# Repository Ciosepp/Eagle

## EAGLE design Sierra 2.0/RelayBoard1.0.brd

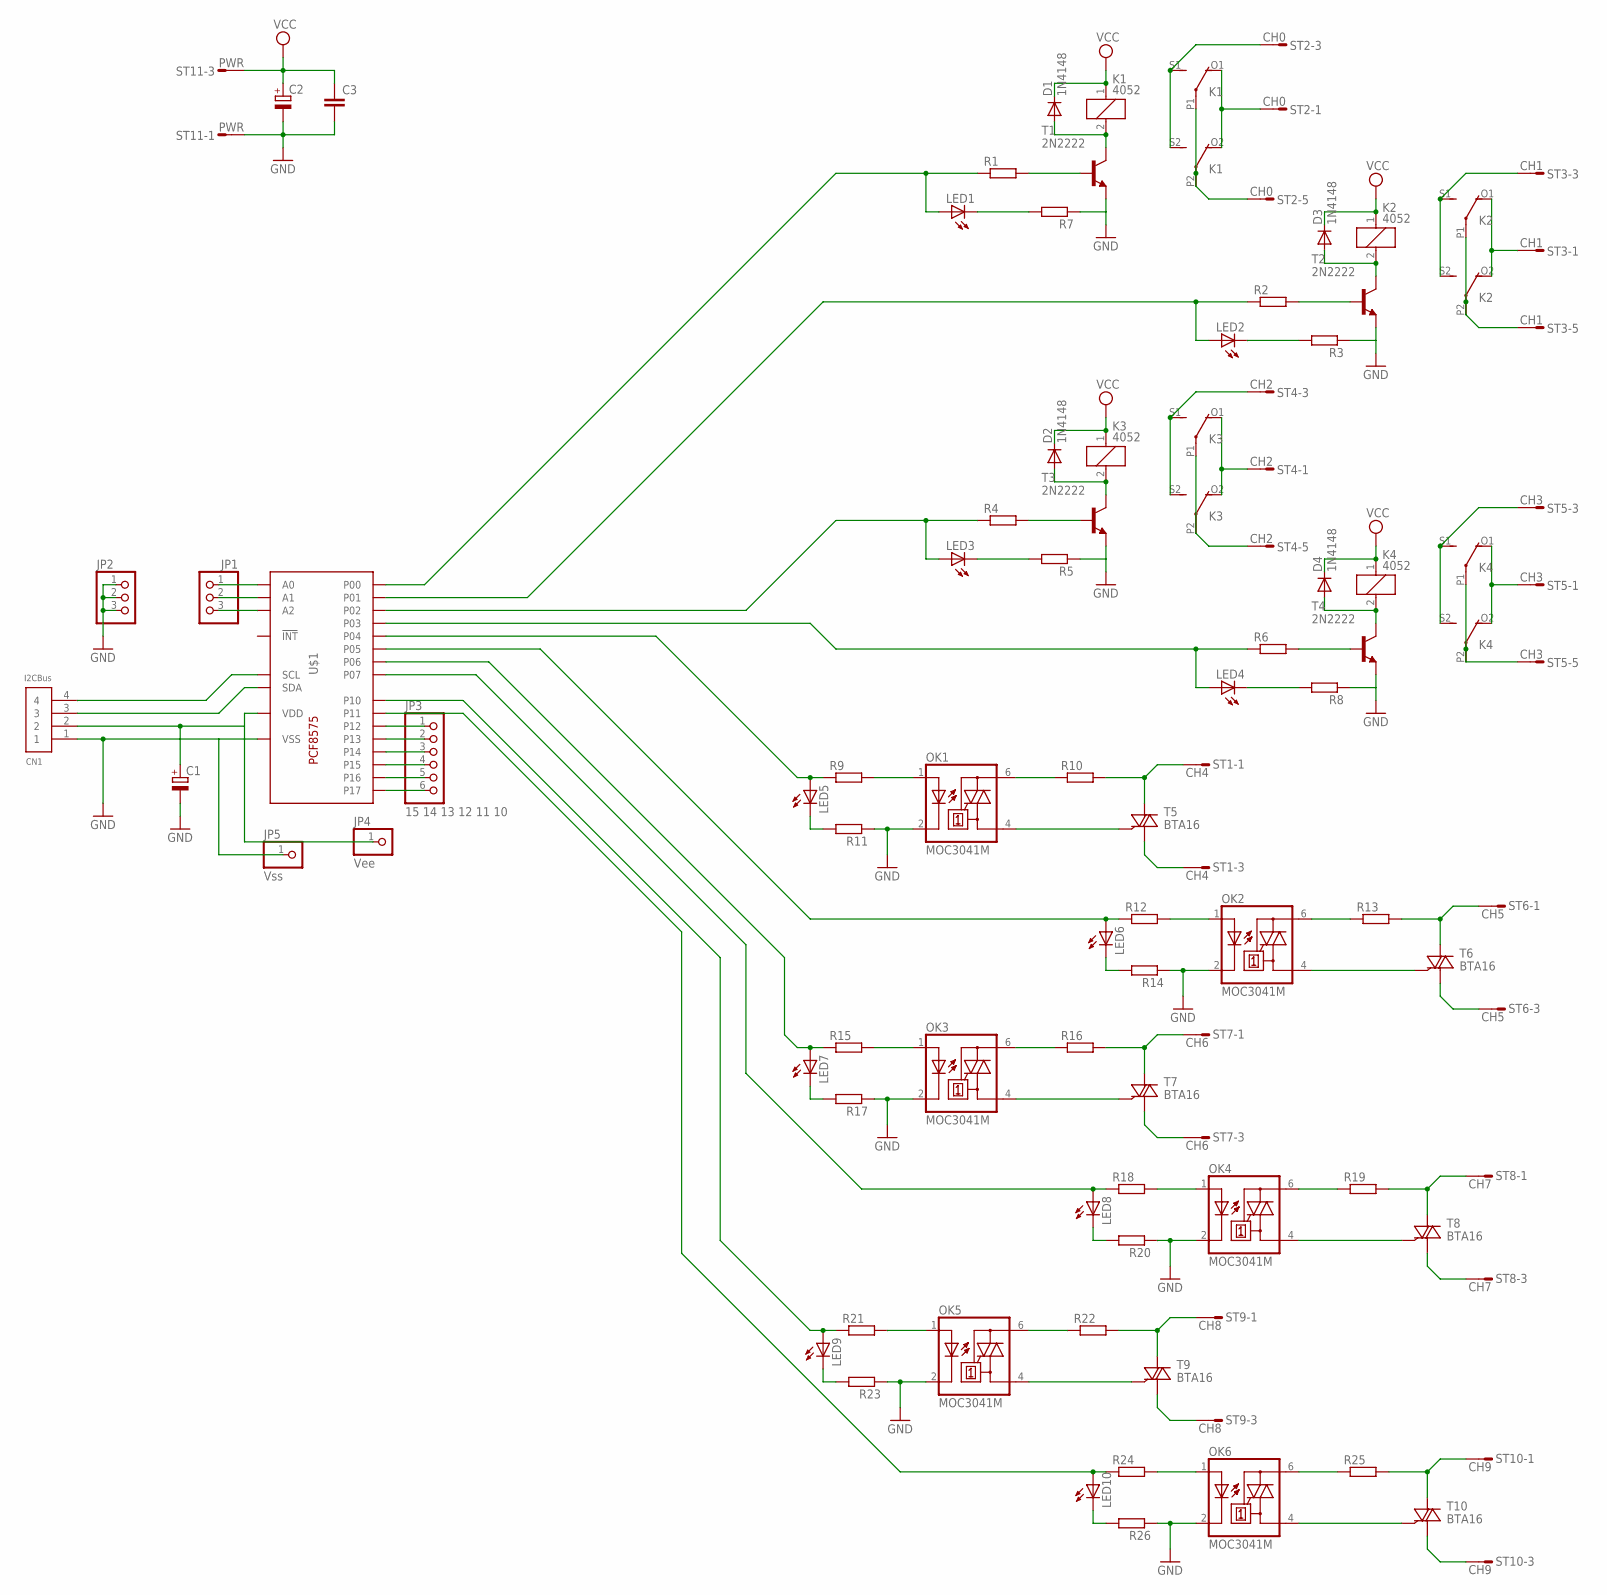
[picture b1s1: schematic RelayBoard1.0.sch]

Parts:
C1: CPOL-EUE3.5-8; E3,5-8
C2: CPOL-EUE2.5-7; E2,5-7
C3: C-EU050-025X075; C050-025X075
CN1: I2CBus; 1X04-BIG
D1, D2, D3, D4: 1N4148; DO35-7
JP1, JP2: PINHD-1X3; 1X03
JP3: 15 14 13 12 11 10; 1X06-CLEANBIG
JP4: Vee; 1X01-CLEANBIG
JP5: Vss; 1X01-CLEANBIG
K1, K2, K3, K4: 4052; F4052
LED1, LED2, LED3, LED4: LED3MM
LED5, LED6, LED7, LED8, LED9, LED10: LEDCHIPLED_0805; CHIPLED_0805
OK1, OK2, OK3, OK4, OK5, OK6: MOC3041M; DIL06
R1, R2, R4, R6: R-EU_0204/7; 0204/7
R3, R5, R7, R8, R9, R12, R15, R18, R21, R24: R-EU_0207/2V; 0207/2V
R10, R13, R16, R19, R22, R25: R-EU_0207/7; 0207/7
R11, R14, R17, R20, R23, R26: R-EU_M0805; M0805
ST1: CH4; MSF3
ST2: CH0; MSF5
ST3: CH1; MSF5
ST4: CH2; MSF5
ST5: CH3; MSF5
ST6: CH5; MSF3
ST7: CH6; MSF3
ST8: CH7; MSF3
ST9: CH8; MSF3
ST10: CH9; MSF3
ST11: PWR; MSF3
T1, T2, T3, T4: 2N2222; TO92-EBC-OVAL
T5, T6, T7, T8, T9, T10: BTA16; TO220BV
U$1: PCF8575C; SOP24

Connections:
GND: C1.-, C2.-, C3.2, CN1.1, JP2.1, JP2.2, JP2.3, JP5.1, OK1.2 (C), OK2.2 (C), OK3.2 (C), OK4.2 (C), OK5.2 (C), OK6.2 (C), R3.1, R5.1, R7.1, R8.1, R11.1, R14.1, R17.1, R20.1, R23.1, R26.1, ST11.1, T1.E, T2.E, T3.E, T4.E, U$1.P$12 (VSS)
unnamed: LED1.A, R1.1, U$1.P$4 (P00)
unnamed: C1.+, CN1.2, JP4.1, U$1.P$24 (VDD)
unnamed: LED1.K (C), R7.2
unnamed: LED2.A, R2.1, U$1.P$5 (P01)
unnamed: LED2.K (C), R3.2
unnamed: D3.A, K2.2, T2.C
unnamed: R2.2, T2.B
unnamed: LED3.A, R4.1, U$1.P$6 (P02)
unnamed: LED3.K (C), R5.2
unnamed: D1.A, K1.2, T1.C
unnamed: D2.A, K3.2, T3.C
unnamed: R4.2, T3.B
unnamed: R1.2, T1.B
unnamed: LED4.A, R6.1, U$1.P$7 (P03)
unnamed: LED4.K (C), R8.2
unnamed: D4.A, K4.2, T4.C
unnamed: R6.2, T4.B
unnamed: K2.O1 (O), K2.O2 (O), ST3.1
unnamed: CN1.3, U$1.P$23 (SDA)
unnamed: CN1.4, U$1.P$22 (SCL)
unnamed: JP1.1, U$1.P$21 (A0)
unnamed: JP1.2, U$1.P$2 (A1)
unnamed: JP1.3, U$1.P$3 (A2)
unnamed: LED5.A, R9.1, U$1.P$8 (P04)
unnamed: OK1.1 (A), R9.2
unnamed: ST1.3, T5.T1 (A1)
unnamed: OK1.4 (A1), T5.G
unnamed: OK1.6 (A2), R10.1
unnamed: R10.2, ST1.1, T5.T2 (A2)
unnamed: K1.S1 (S), K1.S2 (S), ST2.3
unnamed: K1.P1, K1.P2, ST2.5
unnamed: K1.O1 (O), K1.O2 (O), ST2.1
unnamed: K3.P1, K3.P2, ST4.5
unnamed: LED5.C, R11.2
unnamed: LED6.A, R12.1, U$1.P$9 (P05)
unnamed: K3.S1 (S), K3.S2 (S), ST4.3
unnamed: OK2.1 (A), R12.2
unnamed: K3.O1 (O), K3.O2 (O), ST4.1
unnamed: OK2.4 (A1), T6.G
unnamed: OK2.6 (A2), R13.1
unnamed: K4.O1 (O), K4.O2 (O), ST5.1
unnamed: K2.S1 (S), K2.S2 (S), ST3.3
unnamed: K2.P1, K2.P2, ST3.5
unnamed: R13.2, ST6.1, T6.T2 (A2)
unnamed: ST6.3, T6.T1 (A1)
unnamed: LED6.C, R14.2
unnamed: LED7.A, R15.1, U$1.P$10 (P06)
unnamed: K4.S1 (S), K4.S2 (S), ST5.3
unnamed: K4.P1, K4.P2, ST5.5
unnamed: OK3.1 (A), R15.2
unnamed: OK3.4 (A1), T7.G
unnamed: OK3.6 (A2), R16.1
unnamed: R16.2, ST7.1, T7.T2 (A2)
unnamed: ST7.3, T7.T1 (A1)
unnamed: LED7.C, R17.2
unnamed: LED8.A, R18.1, U$1.P$11 (P07)
unnamed: OK4.1 (A), R18.2
unnamed: OK4.4 (A1), T8.G
unnamed: OK4.6 (A2), R19.1
unnamed: R19.2, ST8.1, T8.T2 (A2)
unnamed: ST8.3, T8.T1 (A1)
unnamed: LED8.C, R20.2
unnamed: LED9.A, R21.1, U$1.P$13 (P10)
unnamed: OK5.1 (A), R21.2
unnamed: OK5.4 (A1), T9.G
unnamed: OK5.6 (A2), R22.1
unnamed: R22.2, ST9.1, T9.T2 (A2)
unnamed: ST9.3, T9.T1 (A1)
unnamed: LED9.C, R23.2
unnamed: LED10.A, R24.1, U$1.P$14 (P11)
unnamed: OK6.1 (A), R24.2
unnamed: OK6.4 (A1), T10.G
unnamed: OK6.6 (A2), R25.1
unnamed: R25.2, ST10.1, T10.T2 (A2)
unnamed: ST10.3, T10.T1 (A1)
unnamed: LED10.C, R26.2
unnamed: JP3.1, U$1.P$15 (P12)
unnamed: JP3.2, U$1.P$16 (P13)
unnamed: JP3.3, U$1.P$17 (P14)
unnamed: JP3.4, U$1.P$18 (P15)
unnamed: JP3.5, U$1.P$19 (P16)
unnamed: JP3.6, U$1.P$20 (P17)
VCC: C2.+, C3.1, D1.C, D2.C, D3.C, D4.C, K1.1, K2.1, K3.1, K4.1, ST11.3

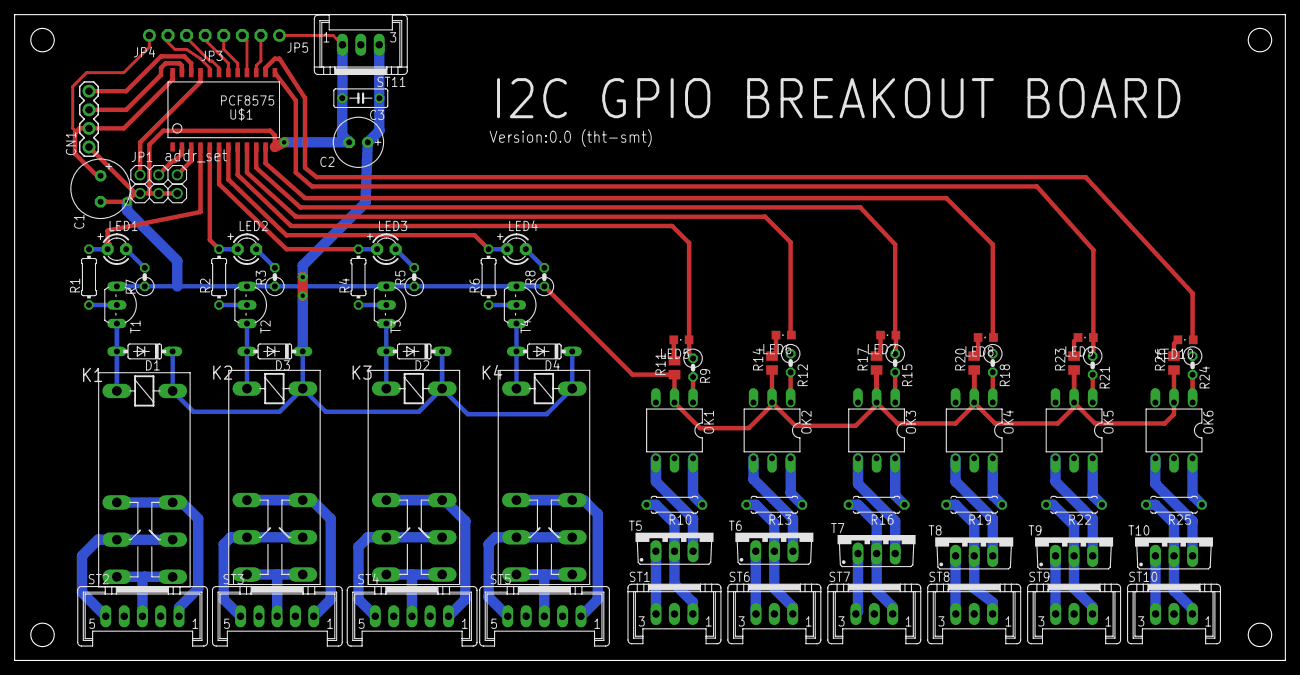
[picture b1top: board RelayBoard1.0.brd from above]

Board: 2 copper layers, 173.7 x 88.3 mm, 81 parts (0 on the bottom side), 84 nets.

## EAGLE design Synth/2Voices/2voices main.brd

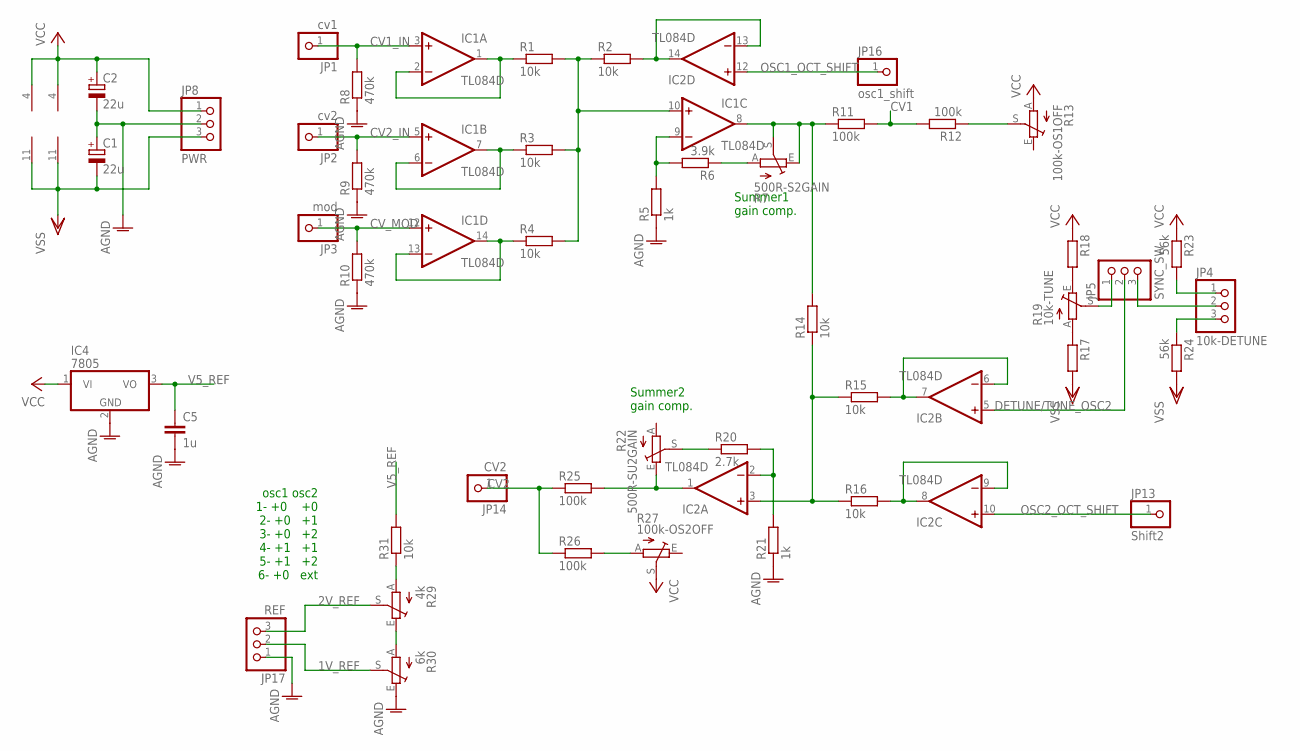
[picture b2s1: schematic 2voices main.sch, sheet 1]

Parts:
C1, C2: 22u; E2,5-7
C5: 1u; C0805
IC1, IC2: TL084D; SO14
IC4: 7805; TO220V
JP1: cv1; 1X01
JP2: cv2; 1X01
JP3: mod; 1X01
JP4: 10k-DETUNE; 1X03
JP5: SYNC_SW; 1X03
JP8: PWR; 1X03
JP13: Shift2; 1X01
JP14: CV2; 1X01
JP16: osc1_shift; 1X01
JP17: REF; 1X03
R1, R2, R3, R4, R14, R15, R16, R31: 10k; R0805
R5, R21: 1k; R0805
R6: 3.9k; R0805
R7: 500R-S2GAIN; S63S
R8, R9, R10: 470k; R0805
R11, R12, R25, R26: 100k; R0805
R13: 100k-OS1OFF; S63S
R17, R18: R-EU_R0805; R0805
R19: 10k-TUNE; S63S
R20: 2.7k; R0805
R22: 500R-SU2GAIN; S63S
R23, R24: 56k; R0805
R27: 100k-OS2OFF; S63S
R29: 4k; S63S
R30: 6k; S63S

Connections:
1V_REF: JP17.2, R30.S
2V_REF: JP17.3, R29.S
AGND: C1.+, C2.-, C5.2, IC4.2 (GND), JP8.2, JP17.1, R5.1, R8.1, R9.1, R10.1, R21.1, R30.E; also elsewhere on the board
CV1: R11.2, R12.2
CV1_IN: IC1.3 (+IN), JP1.1, R8.2
CV2: JP14.1, R25.1, R26.1
CV2_IN: IC1.5 (+IN), JP2.1, R9.2
CV_MOD: IC1.12 (+IN), JP3.1, R10.2
DETUNE/TUNE_OSC2: IC2.5 (+IN), JP5.2
unnamed: IC2.13 (-IN), IC2.14 (OUT), R2.2
unnamed: R29.E, R30.A
unnamed: IC1.1 (OUT), IC1.2 (-IN), R1.1
unnamed: R17.1, R19.A
unnamed: IC1.6 (-IN), IC1.7 (OUT), R3.1
unnamed: IC1.13 (-IN), IC1.14 (OUT), R4.1
unnamed: IC1.10 (+IN), R1.2, R2.1, R3.2, R4.2
unnamed: IC1.9 (-IN), R5.2, R6.2
unnamed: R6.1, R7.A
unnamed: R29.A, R31.1
unnamed: R12.1, R13.S
unnamed: IC1.8 (OUT), R7.E, R7.S, R11.1, R14.2
unnamed: R18.2, R19.E
unnamed: IC2.1 (OUT), R22.E, R25.2
unnamed: R20.1, R22.S
unnamed: IC2.2 (-IN), R20.2, R21.2
unnamed: IC2.3 (+IN), R14.1, R15.1, R16.1
unnamed: IC2.6 (-IN), IC2.7 (OUT), R15.2
unnamed: JP4.1, R23.2
unnamed: JP4.3, R24.1
unnamed: JP4.2, JP5.3
unnamed: JP5.1, R19.S
unnamed: IC2.8 (OUT), IC2.9 (-IN), R16.2
unnamed: R26.2, R27.A
OSC1_OCT_SHIFT: IC2.12 (+IN), JP16.1
OSC2_OCT_SHIFT: IC2.10 (+IN), JP13.1
V5_REF: C5.1, IC4.3 (VO), R31.2
VCC: C2.+, IC1.4 (V+), IC2.4 (V+), IC4.1 (VI), JP8.1, R13.A, R18.1, R23.1, R27.S; also elsewhere on the board
VSS: C1.-, IC1.11 (V-), IC2.11 (V-), JP8.3, R17.2, R24.2; also elsewhere on the board

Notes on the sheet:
osc1 osc2 1- +0 +0 2- +0 +1 3- +0 +2 4- +1 +1 5- +1 +2 6- +0 ext
Summer1 gain comp.
Summer2 gain comp.

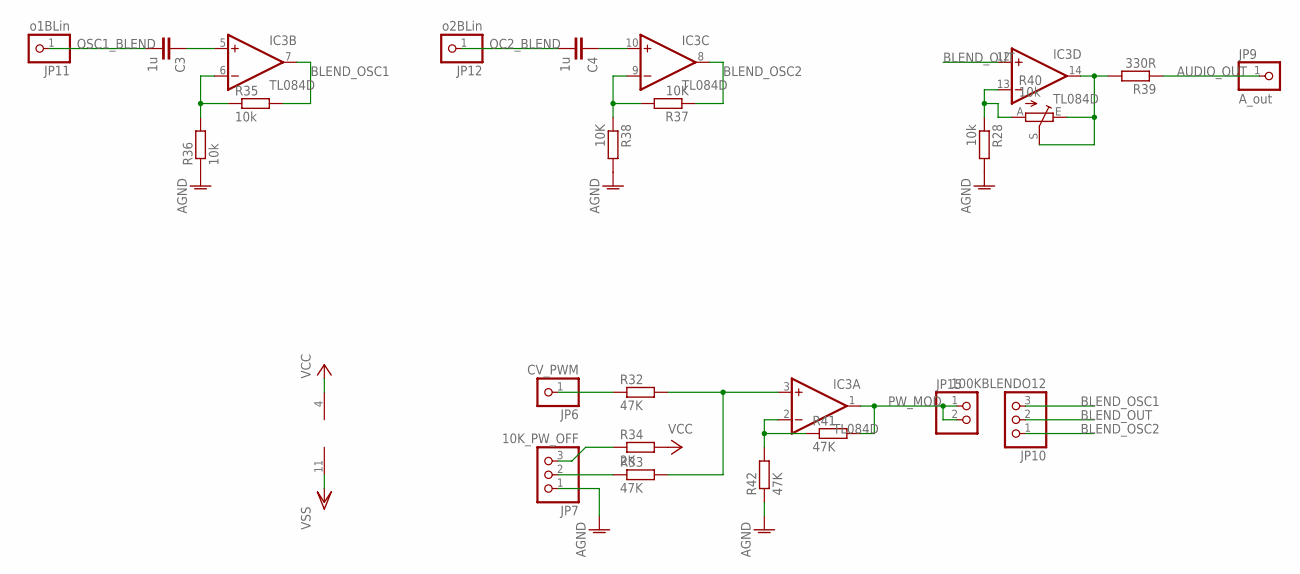
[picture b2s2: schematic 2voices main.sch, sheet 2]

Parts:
C3, C4: 1u; C0805
IC3: TL084D; SO14
JP6: CV_PWM; 1X01
JP7: 10K_PW_OFF; 1X03
JP9: A_out; 1X01
JP10: 100KBLENDO12; 1X03
JP11: o1BLin; 1X01
JP12: o2BLin; 1X01
JP15: PINHD-1X2; 1X02
R28, R35, R36: 10k; R0805
R32, R33, R41, R42: 47K; R0805
R34: 2K; R0805
R37, R38: 10K; R0805
R39: 330R; R0805
R40: 10k; S63S

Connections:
AGND: JP7.1, R28.2, R36.1, R38.2, R42.1; also elsewhere on the board
AUDIO_OUT: JP9.1, R39.1
BLEND_OSC1: IC3.7 (OUT), JP10.3, R35.2
BLEND_OSC2: IC3.8 (OUT), JP10.1, R37.1
BLEND_OUT: IC3.12 (+IN), JP10.2
unnamed: C3.1, IC3.5 (+IN)
unnamed: JP6.1, R32.1
unnamed: JP7.2, R33.1
unnamed: JP7.3, R34.1
unnamed: IC3.13 (-IN), R28.1, R40.A
unnamed: IC3.3 (+IN), R32.2, R33.2
unnamed: IC3.6 (-IN), R35.1, R36.2
unnamed: IC3.9 (-IN), R37.2, R38.1
unnamed: IC3.14 (OUT), R39.2, R40.E, R40.S
unnamed: C4.1, IC3.10 (+IN)
unnamed: IC3.2 (-IN), R41.1, R42.2
OC2_BLEND: C4.2, JP12.1
OSC1_BLEND: C3.2, JP11.1
PW_MOD: IC3.1 (OUT), JP15.1, JP15.2, R41.2
VCC: IC3.4 (V+), R34.2; also elsewhere on the board
VSS: IC3.11 (V-); also elsewhere on the board

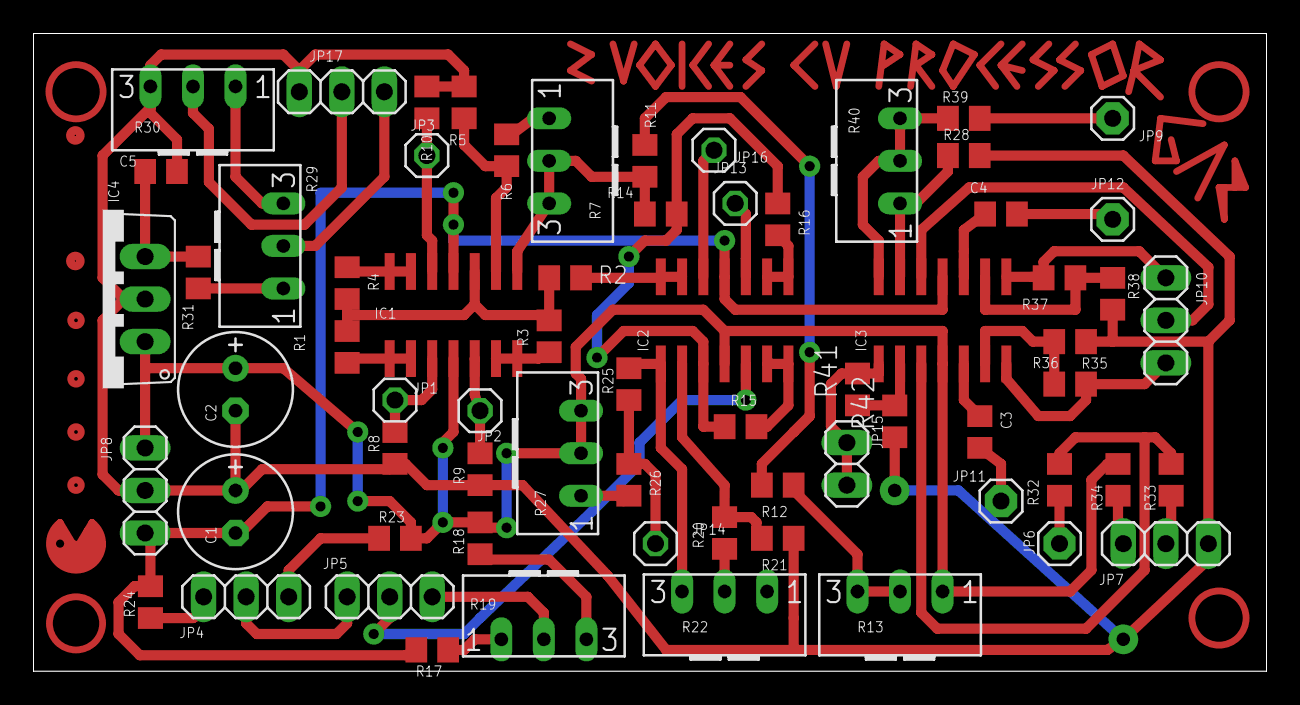
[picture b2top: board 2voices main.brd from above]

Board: 2 copper layers, 73.6 x 38.1 mm, 68 parts (0 on the bottom side), 56 nets.

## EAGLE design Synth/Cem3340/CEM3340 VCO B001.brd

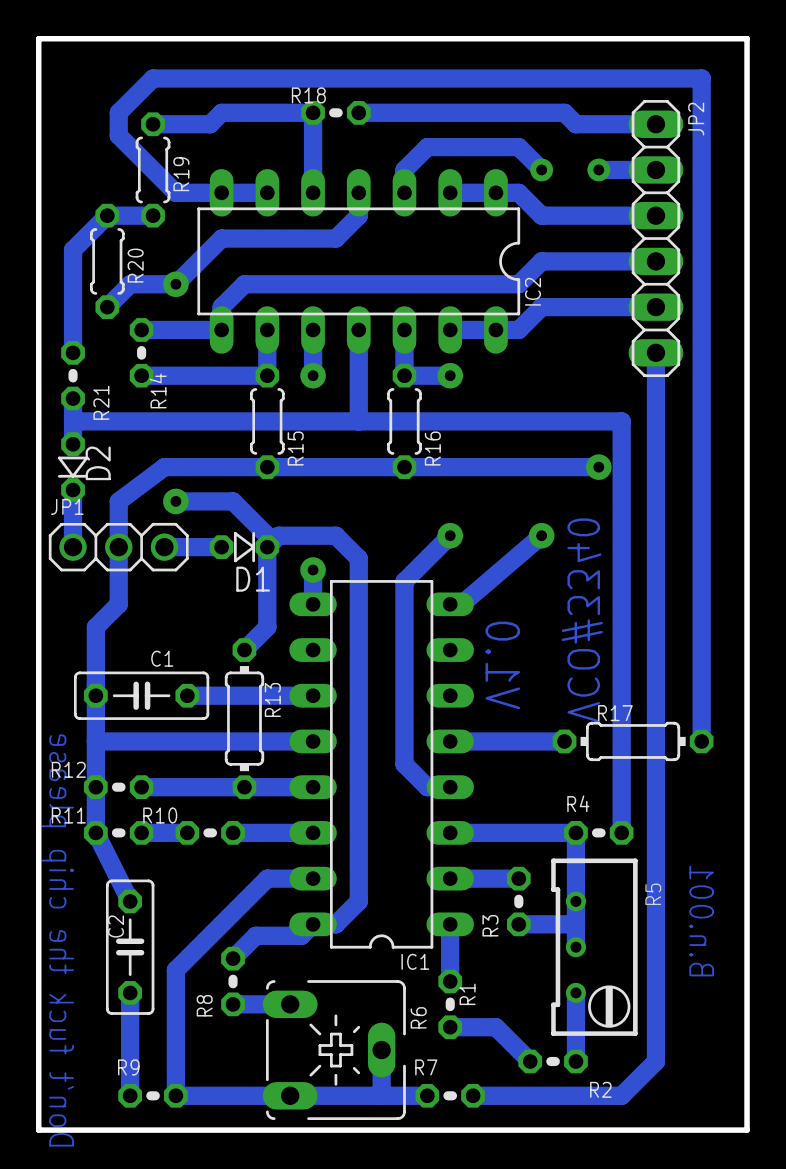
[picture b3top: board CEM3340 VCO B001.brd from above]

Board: 2 copper layers, 39.4 x 60.6 mm, 29 parts (0 on the bottom side), 30 nets.

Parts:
C1, C2: C050-025X075
D1, D2: D-2.5
IC1: CEM3340; DIL16
IC2: TL084P; DIL14
JP1: 1X03
JP2: 1X06
R1, R2, R3, R4, R7, R8, R9, R10, R11, R12, R14, R18, R21: 0204V
R5: RTRIM64W
R6: CA6V
R13, R17: 0204/7
R15, R16, R19, R20: 0204/5

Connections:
GND: C1.1, C2.2, IC1.12, JP1.2, JP2.2, R11.1, R12.2, R15.2, R16.2
unnamed: IC1.1, R1.2
unnamed: R1.1, R2.2
unnamed: R2.1, R5.3
unnamed: IC1.3, R3.1, R4.2, R5.1, R5.2
unnamed: IC1.14, R10.2
unnamed: IC1.2, R3.2
unnamed: R10.1, R11.2
unnamed: IC1.13, R12.1, R13.2
unnamed: JP2.6, R7.2
unnamed: C1.2, IC1.11
unnamed: IC2.1, IC2.2, JP2.3
unnamed: IC1.8, IC2.3
unnamed: R6.A, R8.1
unnamed: IC1.5, R17.1
unnamed: IC1.15, R6.E, R6.S, R7.1, R9.2
unnamed: C2.1, R9.1
unnamed: IC2.9, R14.2, R15.1
unnamed: IC2.8, JP2.4, R14.1
unnamed: IC1.9, IC2.10
unnamed: IC2.13, IC2.14, JP2.5
unnamed: JP2.1, R18.2
unnamed: IC1.4, IC2.12, R16.1
unnamed: IC2.6, IC2.7, R17.2
unnamed: R19.2, R20.2, R21.1
unnamed: IC2.5, R18.1, R19.1
unnamed: D1.A, JP1.3
unnamed: D2.C, JP1.1
V+: D1.C, IC1.16, IC2.4, R8.2, R13.1, R20.1
V-: D2.A, IC2.11, R4.1, R21.2

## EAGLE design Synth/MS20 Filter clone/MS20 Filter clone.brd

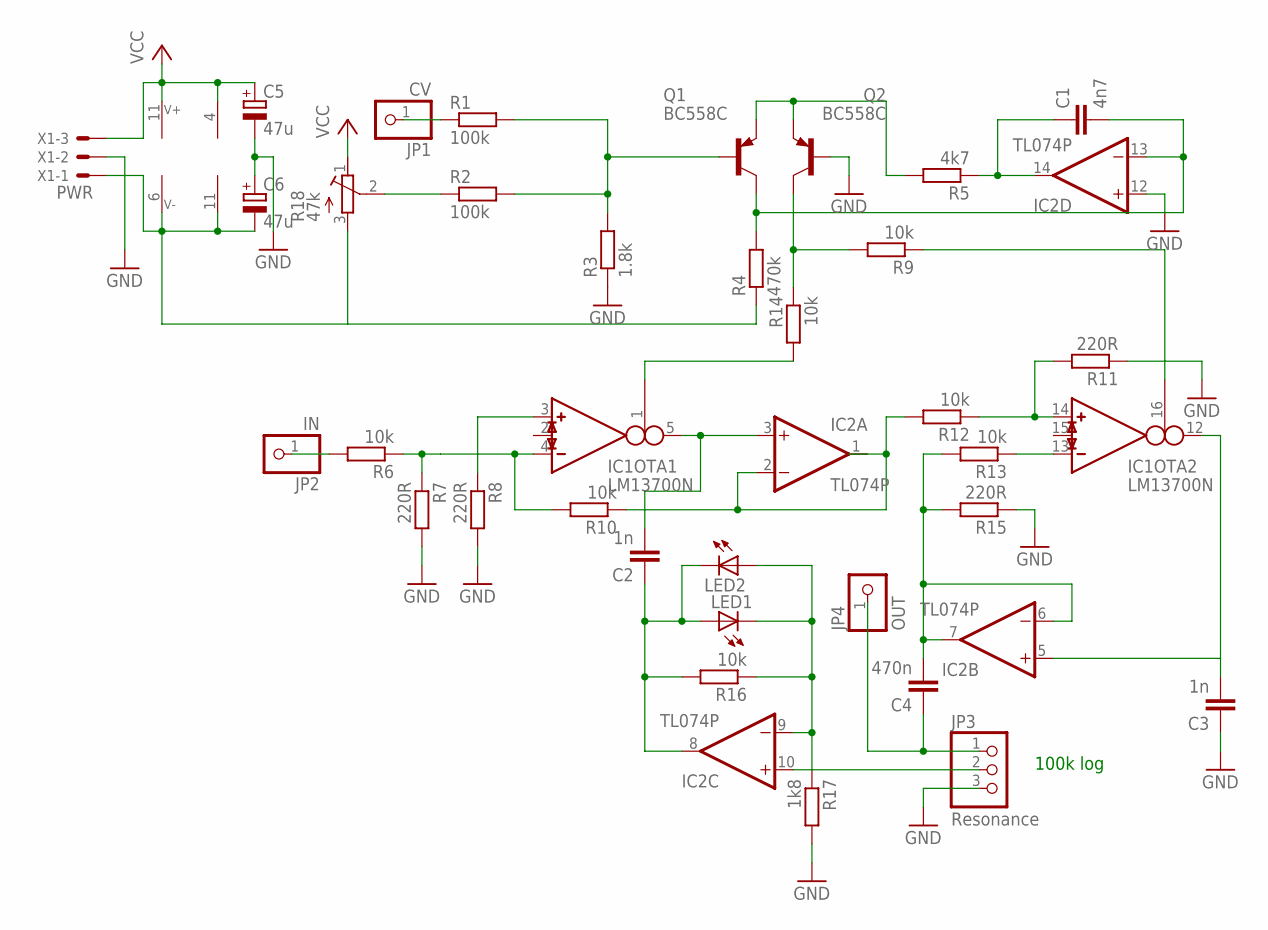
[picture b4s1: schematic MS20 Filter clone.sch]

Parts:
C1: 4n7; C050-024X044
C2, C3: 1n; C050-024X044
C4: 470n; C050-024X044
C5, C6: 47u; E2,5-6
IC1: LM13700N; DIL16
IC2: TL074P; DIL14
JP1: CV; 1X01
JP2: IN; 1X01
JP3: Resonance; 1X03-CLEANBIG
JP4: OUT; 1X01
LED1, LED2: LED5MM
Q1, Q2: BC558C; TO92-EBC
R1: 100k; 0204/5
R2: 100k; 0204/7
R3: 1.8k; 0204/7
R4: 470k; 0204/7
R5: 4k7; 0204V
R6, R9, R12: 10k; 0204/7
R7, R8: 220R; 0204/7
R10, R13: 10k; 0204/5
R11: 220R; 0204/5
R14, R16: 10k; 0204V
R15: 220R; 0204V
R17: 1k8; 0204V
R18: 47k; RTRIMT93YA
X1: PWR; JST-XH-03-PACKAGE-LONG-PAD

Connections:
GND: C3.1, C5.-, C6.+, IC2.12 (+IN), JP3.3, Q2.B, R3.1, R7.2, R8.2, R11.1, R15.1, R17.2, X1.2
unnamed: Q1.B, R1.2, R2.2, R3.2
unnamed: R2.1, R18.2 (S)
unnamed: C1.2, IC2.13 (-IN), Q1.C, R4.2
unnamed: JP1.1, R1.1
unnamed: Q1.E, Q2.E, R5.2
unnamed: IC2.9 (-IN), LED1.K (C), LED2.A, R16.1, R17.1
unnamed: C1.1, IC2.14 (OUT), R5.1
unnamed: Q2.C, R9.2, R14.1
unnamed: IC1.1 (I_BIAS), R14.2
unnamed: JP2.1, R6.2
unnamed: IC1.16 (I_BIAS), R9.1
unnamed: IC1.4 (IN_N), R6.1, R7.1, R10.2
unnamed: IC1.3 (IN_P), R8.1
unnamed: C2.2, IC1.5 (OUT), IC2.3 (+IN)
unnamed: IC2.2 (-IN), R10.1, R12.2
unnamed: IC1.14 (IN_P), R11.2, R12.1
unnamed: C4.2, IC2.6 (-IN), IC2.7 (OUT), R13.2, R15.2
unnamed: IC1.13 (IN_N), R13.1
unnamed: C3.2, IC1.12 (OUT), IC2.5 (+IN)
unnamed: IC2.10 (+IN), JP3.2
unnamed: C2.1, IC2.8 (OUT), LED1.A, LED2.K (C), R16.2
unnamed: C4.1, JP3.1, JP4.1
V-: C6.-, IC1.6 (V-), IC2.11 (V-), R4.1, R18.3 (A), X1.1
VCC: C5.+, IC1.11 (V+), IC2.4 (V+), R18.1 (E), X1.3

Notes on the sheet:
100k log

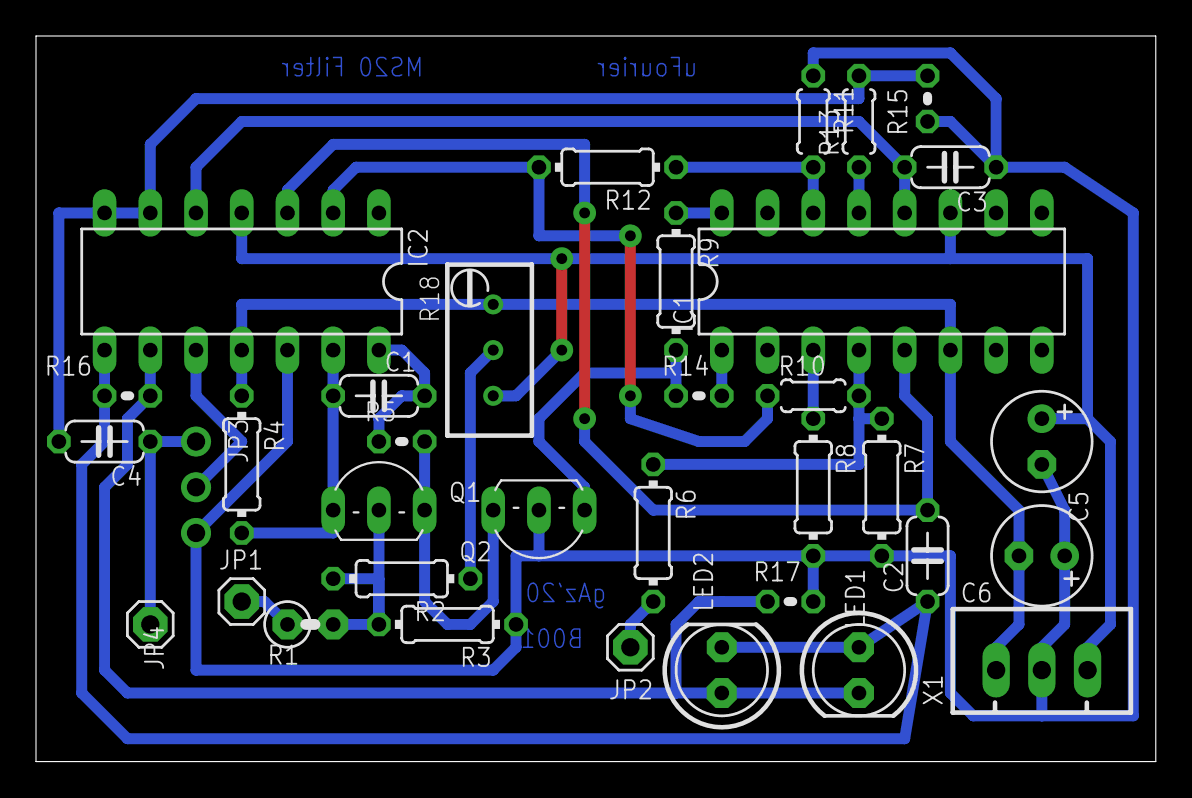
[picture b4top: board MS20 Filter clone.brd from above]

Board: 2 copper layers, 62.2 x 40.3 mm, 35 parts (0 on the bottom side), 25 nets.

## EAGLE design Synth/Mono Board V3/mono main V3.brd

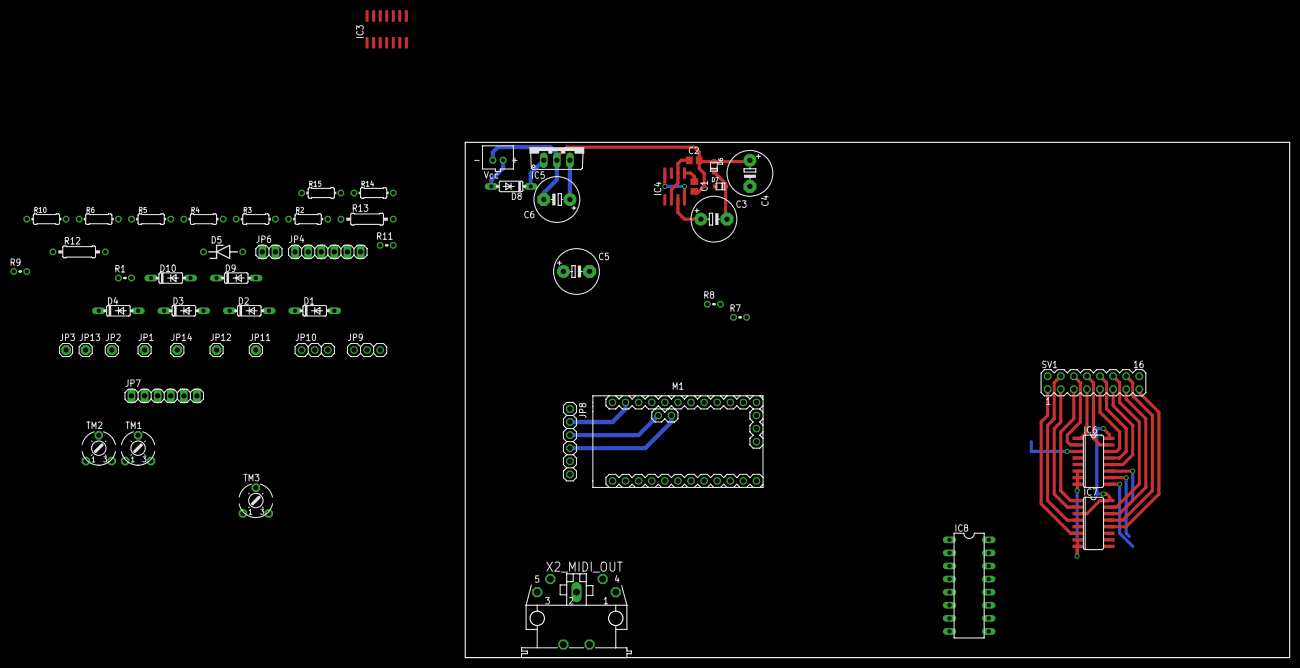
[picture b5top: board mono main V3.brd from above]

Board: 2 copper layers, 160.0 x 100.0 mm, 57 parts (0 on the bottom side), 66 nets.

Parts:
C1, C2: C0805
C3: 47u; E5-8,5
C4: 47; E5-8,5
C5, C6: E5-8,5
CN1: Vcc; JST-PH-2-THM
D1, D2, D3, D4, D9, D10: 1N4148; DO35-7
D5: ZDIO-7.5
D6: 4148; SOD-323F
D7: 1N4148; SOD-323F
D8: 4148; DO35-7
IC3: TL084D; SO14
IC4: NE555D; SO08
IC5: 7805; TO220V
IC6, IC7: 4051D; SO16
IC8: 4040N; DIL16
JP1: CK_O; 1X01
JP2: GATE; 1X01
JP3: CV; 1X01
JP4: 1X06
JP6: 1X02
JP7: CK_ division_rotor; 1X06
JP8: DAC; 1X06
JP9: pitch_bend; 1X03
JP10: expression; 1X03
JP11: CV_Bend; 1X01
JP12: Exp_out; 1X01
JP13: Bend; 1X01
JP14: Exp_IN; 1X01
M1: ARDUINO-PRO-MINI-5.0V#NP; ARDUINO-PRO-MINI#NP
R1: 330; 0204V
R2, R3: 330; 0204/7
R4: 300; 0204/7
R5, R14, R15: 10k; 0204/7
R6: 1k; 0204/7
R7, R8, R11: 10k; 0204V
R9: 470; 0204V
R10: 100; 0204/7
R12, R13: 10k; 0207/10
SV1: keyboard connector; MA08-2
TM1, TM2: 6MM
TM3: 50k; 6MM
X2_MIDI_OUT: MAB5SH

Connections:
-3V: C5.-, D5.A, R9.2, TM2.A
AGND: C1.2, C2.2, C4.+, C5.+, C6.-, CN1.2, D3.A, D4.A, D5.C, D6.A, D10.A, IC3.11, IC4.1, IC5.2, IC6.6, IC6.7, IC6.8, IC7.7, IC7.8, IC8.11, JP8.2, JP8.6, JP10.1, M1.J6.2, R5.1, R6.1, R12.1, R13.2, X2_MIDI_OUT.2
ARP_ENABLE: JP4.4, M1.J6.7, R6.2
ARP_MODE: JP4.5, M1.J6.8
CK_I: JP7.1, M1.J7.6
CK_O: D2.A, D4.C, JP6.2, M1.J7.8, R3.2
CK_RATE: JP4.3, M1.J6.6
CV: IC3.3, JP8.1
GATE: D1.A, D3.C, M1.J7.7, R4.2
unnamed: JP3.1, R10.2
unnamed: JP1.1, R3.1
unnamed: IC8.9, JP7.3
unnamed: IC8.7, JP7.4
unnamed: IC8.6, JP7.5
unnamed: IC8.5, JP7.6
unnamed: D9.A, D10.C, IC8.10, JP6.1, JP7.2
unnamed: JP2.1, R4.1
unnamed: R2.2, X2_MIDI_OUT.5
unnamed: R1.1, X2_MIDI_OUT.4
unnamed: IC3.9, R13.1, TM3.A
unnamed: IC4.7, R7.2, R8.2
unnamed: C2.1, IC4.2, IC4.6, R7.1
unnamed: C1.1, IC4.5
unnamed: IC3.1, IC3.2, R10.1, R15.2
unnamed: C3.+, IC4.3
unnamed: C3.-, D6.C, D7.C
unnamed: C4.-, D7.A, R9.1
unnamed: IC3.12, JP9.2
unnamed: IC3.13, IC3.14, JP13.1, R14.2
unnamed: JP9.3, TM1.A
unnamed: IC3.10, JP10.2
unnamed: IC3.8, JP12.1, TM3.E, TM3.S
unnamed: CN1.1, D8.A
unnamed: JP9.1, TM2.S
unnamed: IC3.6, R11.2, R12.2
unnamed: IC3.7, JP11.1, R11.1
unnamed: IC3.5, R14.1, R15.1
unnamed: JP10.3, JP14.1
OCT_SEL: JP4.2, M1.J6.5
PE: X2_MIDI_OUT.PE, X2_MIDI_OUT.PE@
R1: IC6.2, SV1.6
R2: IC6.1, SV1.7
R3: IC6.15, SV1.8
R4: IC6.14, SV1.9
R5: IC6.13, SV1.10
R6: IC6.12, SV1.11
R_MUX: IC6.3, M1.J7.1, R5.2
R_MUX_A: IC6.11, M1.J7.4
R_MUX_B: IC6.10, M1.J7.3
R_MUX_C: IC6.9, M1.J7.2
SCK: JP8.3, M1.J2.2
SDA: JP8.4, M1.J2.1
VCC: C6.+, D1.C, D2.C, D9.C, IC5.3, IC6.16, IC7.3, IC7.16, JP4.1, JP8.5, M1.J6.4, R1.2, TM1.S
VCC_RAW: D8.C, IC3.4, IC4.4, IC4.8, IC5.1, M1.J6.1, R8.1
W1: IC7.6, M1.J6.9, SV1.1
W2: IC7.5, SV1.2
W3: IC7.2, SV1.3
W4: IC7.4, SV1.4
W5: IC7.1, SV1.5
W6: IC7.15, SV1.12
W7: IC7.14, SV1.13
W8: IC7.13, SV1.14
W9: IC7.12, SV1.15
W_MUX_A: IC7.11, M1.J6.12
W_MUX_B: IC7.10, M1.J6.11
W_MUX_C: IC7.9, M1.J6.10

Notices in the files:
parts and their libraries:
diy-modules: Released under the Creative Commons Attribution 4.0 International License: http://creativecommons.org/licenses/by/4.0
